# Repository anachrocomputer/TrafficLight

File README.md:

# TrafficLight #

Simple PCB design for a traffic light signal head which can be used
with the Arduino.
Just three LEDs, three resistors and a connector.

## Hardware ##

PCB designed with KiCad
(originally KiCad V3, now updated to V6.0.2).
Either 10mm or 8mm LEDs can be fitted.
Best to select black soldermask,
and make the edges of the PCB black with paint or a marker pen.

The board and the parts needed to assemble it.

Two PCBs, assembled with 8mm and 10mm LEDs.

## Software ##

In the subdirectory 'TrafficLight' there's a very simple Arduino
sketch to make the lights change.
The pins assigned to the LEDs can be changed in the code,
so that the PCB can be plugged directly into an Arduino Uno
or an Arduino Nano.

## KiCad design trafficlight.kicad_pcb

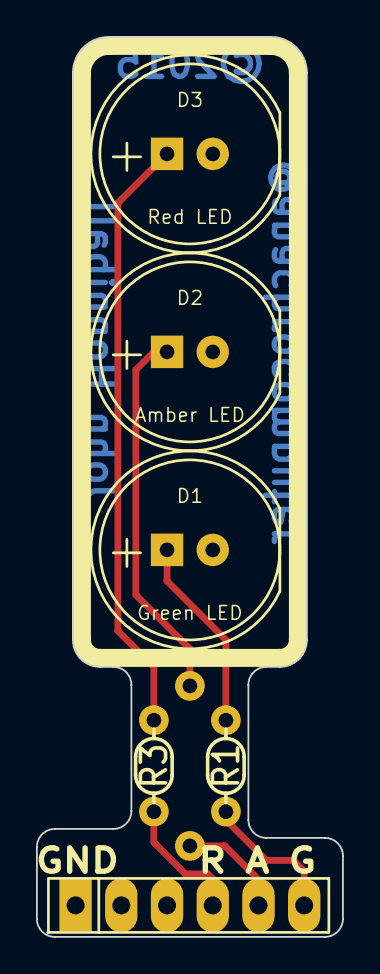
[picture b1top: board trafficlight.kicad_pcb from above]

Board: 2 copper layers, 17.0 x 50.0 mm, 6 parts (1 on the bottom side), 4 nets.

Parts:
D1: Green LED; LED-G-10MM
D2: Amber LED; LED-A-10MM
D3: Red LED; LED-R-10MM
R1, R3: 330R; R2-LARGE_PADS
R2: 330R; R3-5-LARGE_PADS

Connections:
GND: D1.2, D2.2, D3.2
unnamed: D3.1, R3.2
unnamed: D2.1, R2.2
unnamed: D1.1, R1.2

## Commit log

2015-08-02 Initial commit with design that was sent to Dirty PCBs in July 2015.
2015-08-02 Changed LEDs so that we have separate red, amber and green types. This makes the 3D view look right. Needed extra .wrl file for the red one, and will need another if we add blue LEDs.
2015-08-02 Added pin labelling on schematic, for use with Arduino.
2015-08-02 Added title and revision info to schematic.
2015-08-03 Created new resistor footprints for 0.2in and 0.35in pad spacing. Used them to place one resistor on rear of PCB and bring the other two closer together. This allows the column of the traffic light t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
2019-05-07 Add Arduino code (sketch) to drive the traffic light LEDs.
2019-05-07 Expand README to mention Arduino sketch.
2024-05-21 Add photos to README.
2024-10-13 Update to KiCad V4.0.4 as intermediate step.
    Beware: the LEDs seem to have been reversed, pin 1/2 swap. But the PCB still shows pin 1 as the positive terminal, connected to the resistor. Will need to fix that once we've updated all the way to t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
2024-10-13 Add PDF of schematic.
2024-10-19 Update to KiCad V5.1.5 as intermediate step.
    We're aiming for V8.0 but have to go via 4, 5, and 6.
2024-10-19 Turns out we do need trafficlight-cache.lib after all.
2024-10-19 Update version in README.
2024-10-19 Update to KiCad V6.0.2.
    This update renames some of the files. Keep the old ones for now, delete them in a later commit.
2024-10-19 Remove more old files.
2024-10-19 Change resistor footprints.

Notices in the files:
trafficlight.kicad_pcb:
©2015
